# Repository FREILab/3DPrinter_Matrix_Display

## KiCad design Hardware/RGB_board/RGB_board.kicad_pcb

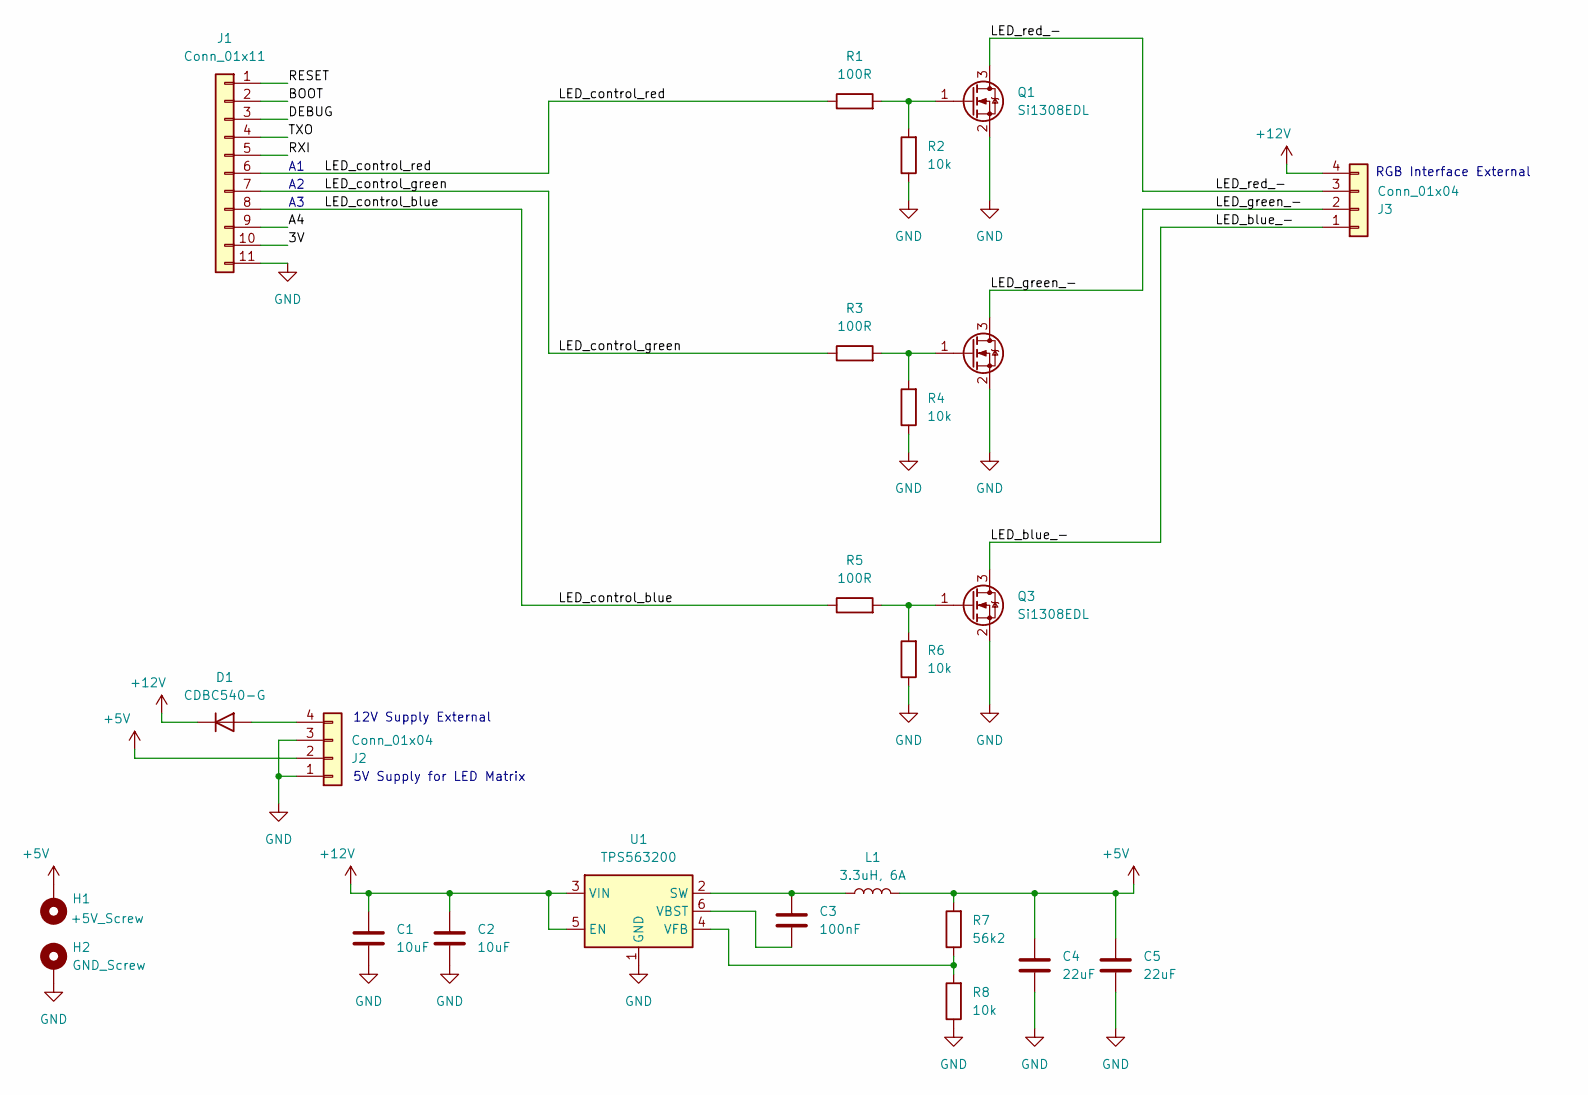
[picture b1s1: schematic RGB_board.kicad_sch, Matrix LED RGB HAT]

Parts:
C1, C2: 10uF; C_0805_2012Metric
C3: 100nF; C_0805_2012Metric
C4, C5: 22uF; C_0805_2012Metric
D1: CDBC540-G; D_SMC
H1: +5V_Screw; H_3.2mm_M3_Pad_7mm
H2: GND_Screw; H_3.2mm_M3_Pad_7mm
J1: Conn_01x11; J_FM11x2_2.5476341-311LF
J2, J3: Conn_01x04; T_4_PhoenixContact_LPT_5_4-H-1x04_Horizontal
L1: 3.3uH, 6A; L_Bourns_SRP7028A_7.3x6.6mm
Q1, Q2, Q3: Si1308EDL; SOT-323_SC-70; Manufacturer Part Number SI1308EDL-T1-BE3; Digikey 742-SI1308EDL-T1-BE3TR-ND
R1, R3, R5: 100R; R_0805_2012Metric; LCSC Part # C17475
R2, R4, R6: 10k; R_0805_2012Metric; LCSC Part # C17414
R7: 56k2; R_0805_2012Metric; LCSC Part # C17475
R8: 10k; R_0805_2012Metric; LCSC Part # C17475
U1: TPS563200; SOT-23-6

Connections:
+5V: C4.1, C5.1, H1.1, J2.2, L1.2, R7.2
+12V: C1.1, C2.1, D1.1 (K), J3.4, U1.3 (VIN), U1.5 (EN)
/3V: J1.10
/A4: J1.9
/BOOT: J1.2
/DEBUG: J1.3
/LED_blue_-: J3.1, Q3.3 (D)
/LED_control_blue: J1.8, R5.1
/LED_control_green: J1.7, R3.1
/LED_control_red: J1.6, R1.1
/LED_green_-: J3.2, Q2.3 (D)
/LED_red_-: J3.3, Q1.3 (D)
/RESET: J1.1
/RXI: J1.5
/TXO: J1.4
GND: C1.2, C2.2, C4.2, C5.2, H2.1, J1.11, J2.1, J2.3, Q1.2 (S), Q2.2 (S), Q3.2 (S), R2.1, R4.1, R6.1, R8.1, U1.1 (GND)
unnamed: D1.2 (A), J2.4
unnamed: Q1.1 (G), R1.2, R2.2
unnamed: Q2.1 (G), R3.2, R4.2
unnamed: Q3.1 (G), R5.2, R6.2
unnamed: C3.1, L1.1, U1.2 (SW)
unnamed: C3.2, U1.6 (VBST)
unnamed: R7.1, R8.2, U1.4 (VFB)

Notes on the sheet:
5V Supply for LED Matrix
RGB Interface External
12V Supply External

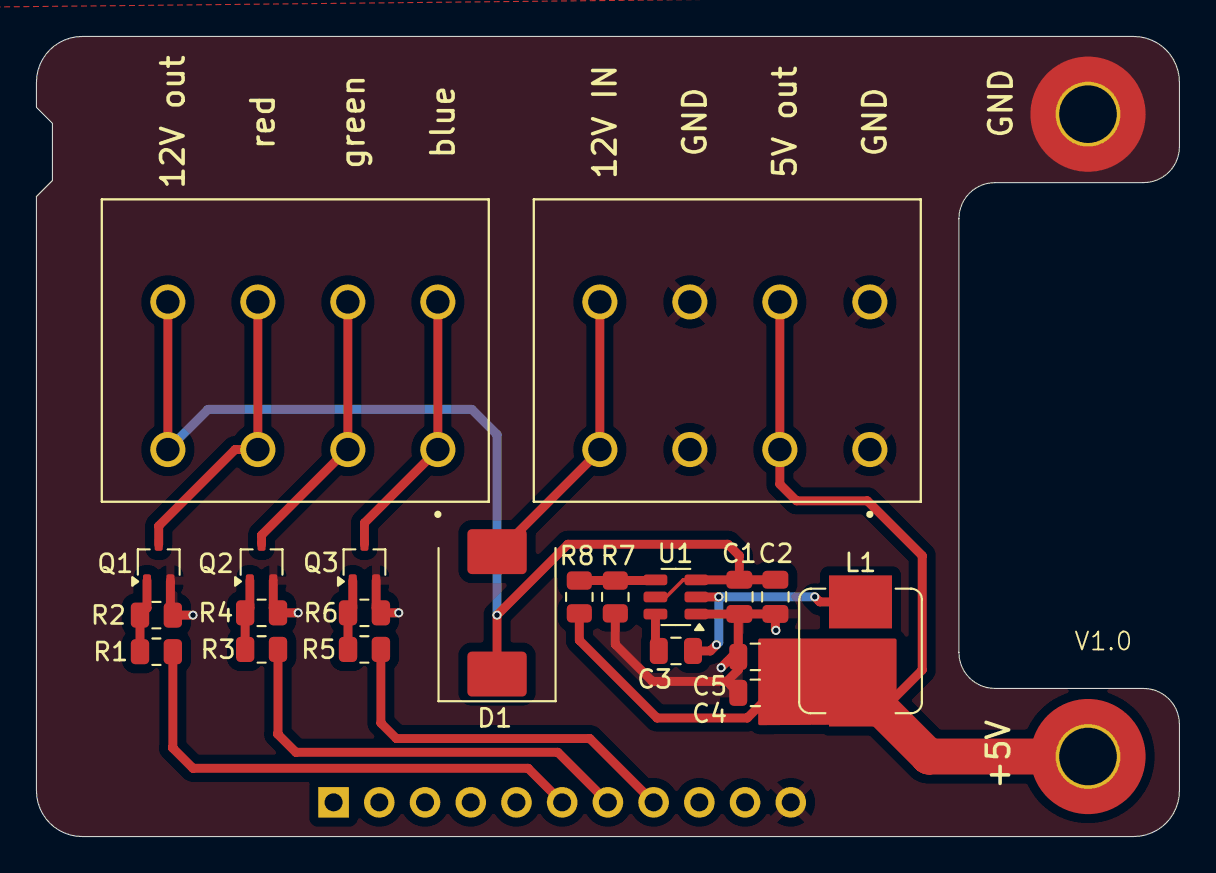
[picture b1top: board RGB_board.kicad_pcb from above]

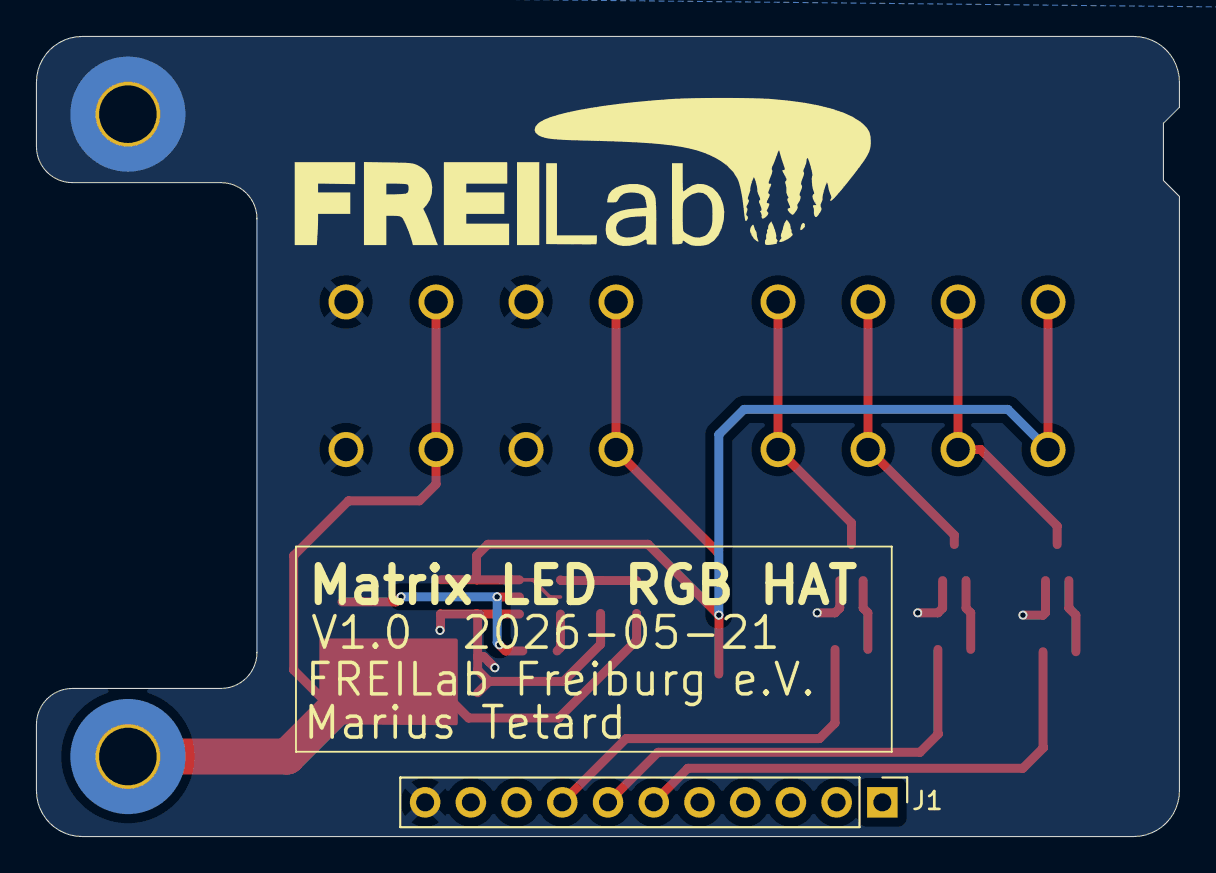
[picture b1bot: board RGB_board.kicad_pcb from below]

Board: 2 copper layers, 63.5 x 44.5 mm, 26 parts (2 on the bottom side), 16 nets.

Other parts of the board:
U$25: S3_MATRIXPORTAL_TOP
U$26: S3_MATRIXPORTAL_BOT

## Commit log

2026-03-03 fix licker
2026-03-03 migrate to platformio
2026-03-03 Add GitHub Actions workflow for multi-printer firmware
2026-03-03 first CI test
2026-03-03 Update GitHub Actions to use latest action versions
2026-03-03 Disable fail-fast in build job strategy
2026-03-03 Fix paths for PlatformIO build and upload steps
2026-03-03 fix flags
2026-03-03 Create dummy secret.h in build workflow
    Add step to create dummy secret.h if it doesn't exist
2026-03-03 rename file
2026-03-03 rename action
2026-03-03 release management
2026-03-03 prep release
2026-03-03 differienciate between keys
2026-03-03 fix naming
2026-03-03 test prusa link
2026-03-03 config CI
2026-03-03 fix confligs in tags
2026-03-03 add missing release
2026-03-08 first hw tests (not qet running)
2026-03-08 clean up comments
2026-04-05 Add Printer 3 to prusaprint
2026-05-07 Update default environment to prusa_drucker_2 and add detailed programming instructions for ESP32-S3 display
2026-05-11 Enhance printer connection status handling
2026-05-11 Add IP address display functionality and configure button handling
2026-05-11 Refactor display programming guide and enhance OTA functionality for ESP32-S3
2026-05-11 Add example configuration file for Wi-Fi credentials and printer settings
2026-05-11 Add status LED control functions and improve light handling logic
2026-05-11 Add task configuration for OTA upload of multiple printers
2026-05-11 Add nozzle temperature handling for unavailable state in display functions
2026-05-12 remove workflow
2026-05-12 Update board configuration to use adafruit_matrixportal_esp32s3 and fix library dependencies
2026-05-15 Add schematic for RGB board with Raspberry Pi connector
    - Created a new schematic file for the RGB board.
    - Included a connector for Raspberry Pi 2/3 with relevant details.
    - Added component information and documentation link for reference.
2026-05-17 Refactor code structure for improved readability and maintainability
2026-05-20 Update component list in ENTWICKLUNGSPLAN.md for RGB board
2026-05-20 große fortschritte, mockup bereit
2026-05-21 ready for production
2026-05-21 some cleanup
2026-05-24 Remove static printer IP addresses and update upload port for prusa_drucker_1_ota
